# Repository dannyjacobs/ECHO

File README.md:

The External Calibrator for Hydrogen Arrays (ECHO) is a system for calibrating wide-field radio frequency arrays using a radio transmitter mounted on a drone.
Primarily targeting (but not exclusively limited to) arrays operating in the sub-GHz band targeting highly redshifted
21cm radiation from the early universe.

This repository contains software for planning missions and analyzing data. It also contains hardware designs for drones and mounts.

This is an open source project. Use and reuse is encouraged.  If you use this code or hardware designs please reference the github repo.
http://github.com/dannyjacobs/ECHO and cite [our 2017 paper](http://adsabs.harvard.edu/abs/2017PASP..129c5002J).  If you have improvements please fork and send a PR!

## Community
* We have an active "Slack Connect" channel, accessible to anyone with a Slack account.  To be invited, email [Danny Jacobs](dcjacob2@asu.edu)
* Project [Web page](http://danielcjacobs.com/ECHO)
* [Code Documentation](https://external-calibrator-for-hydrogen-arrays-echo.readthedocs.io)
* A [mailing list](https://groups.google.com/d/forum/astro_echo) exists

## Installation
Install prerequisites. We recommend the anaconda package manager
* healpy (note that as of Jan 2020 healpy is not available for Windows)
* matplotlib
* numpy
* scipy

Get this repo
`git clone https://github.com/dannyjacobs/ECHO.git`

Install using pip
```
cd ECHO
pip install .
```

## Organization
The code is organized into a few modules. The beam mapping pipeline steps are
1. Read and down-select drone telemetry
2. Read and down-select radio telescope data (varies per telescope, usually spectra vs time)
3. Match up drone positions and telescope measurements. (Sometimes referred to as zippering.)
4. Grid beam (including power map, sample counts and standard deviation)
5. Analyze results. Example analysis steps include:
  1. subtract transmitter model
  2. plot beam maps
  3. plot slices
  4. plot drone events and dynamics
  5. difference beams
### Modules

 #### `plot_utils.py`
 Functions for plotting, but also all functions relating to healpix gridding
 and manipulation including gridding.
  * `grid_to_healpix` :  grids aligned RF power vs XYZ position
 into a healpix map
  * `make_beam` :  downselects desired spectral channel, converts from latlon to XYZ and calls `grid_to_healpix`
  * `project_healpix` :  flattens from spherical healpix map to 2d gnomic projection
  * `rotate_hpm` :  rotates a healpix map about the polar axis. useful for plotting
  * Other functions, most of whom are deprecated.
 #### `read_utils.py`
 Functions for reading and writing drone and beam data. Drone log file formats
 are not well documented and change all the time.
  * `read_map` : replacement for healpy read function that respects nans
  * `write_map`: replacement for healpy write function that respect nans
  * `apm_version`: tries to determine the version of ardupilot that wrote a log file.
  * `read_apm_log_A_B_C` : reads an ardupilot log of version A_B_C
    * returns position_times, positions,
    * attitude_times, attitudes,
    * waypoint_times, waypoint_numbers
  * `read_echo_spectrum` : reads a spectrum data file output by the ECHO spectrum logger ca 2017 (signalhound + get_sh_spectra)
  * `read_orbcomm_spectrum` : reads a spectrum data file output by the Bradley orbcomm system (ca 2017)
  * `channel_select` : given a spectrum, list of frequencies, and desired frequency returns closest frequency and spectrum amplitude
  * `interp_rx`: interpolates received power onto the measured position time grid
  * `flag_angles` : flags outlier yaws input times,yaw_angles return matching flag array
  * `flag_waypoints` : flags a range of time around a list of waypoints
  * `apply_flagtimes` : Given a list of bad times, a buffer size and a time array, generate a flag table.
#### `position_utils.py`
 * `latlon2xy` : about what you think
 * `to_spherical` : xyz to spherical
#### `time_utils.py`
Most of these are of dubious necessity.
 * `unix_to_gps` : thin wrapper around astropy.Time
 * `gps_to_HMS` : convert GPS time to Hours Minutes Seconds, thin wrapper around
#### `server_utils.py`
Stuff developed to support real-time operations. This never worked very well with mavlink.
### Scripts
#### Jacobs 2017
Scripts used in the 2017 paper are all run in [one master shell script](https://github.com/dannyjacobs/ECHO_paper1/blob/master/scripts/make_plots.sh)
 * plot_yaw.py
 * plot_GB_pos_power_interp.py
 * ECHO_zipper.py
 * ECHO_mk_beam.py
 * plot_ECHO_GB_power_rms_counts.py
 * plot_ECHO_GB_maps.py
 * plot_GB_slices.py
 * ECHO_sub_tx_beam.py
 * plot_ECHO_GB_ratios.py
 * plot_GB_avg_slices.py
 * plot_MWAtile_slices.py
 * MWATilemodel2hpm.py
 * combine_MWAtile_maps.py

 #### Utility Scripts
  * valon_readwrite.py : program the valon transmitter
  * gen_spherical_flight_path.py : generate waypoints in a healpix pattern
  * CST_to_healpix.py : convert the beam file from CST Microwave studio to a healpix map. Note that this should eventually be replaced with [pyuvbeam](https://github.com/RadioAstronomySoftwareGroup/pyuvdata/blob/master/pyuvdata/uvbeam.py).

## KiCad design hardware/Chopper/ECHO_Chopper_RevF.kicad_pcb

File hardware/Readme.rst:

.. csv-table:: ECHO Version Summary
   :header: "Version", "Drone Make", "Drone Frame", "Drone Name", "Tx Mount", "Transmitter", "Antenna", "Flight Software"
   :widths: auto

   "1", "Mystery Inc.", "Octo", "Brain", " ", " ", "BicoLOG 5070", " "
   "2", "Flamewheel", "Quad", "Crater", " ", " ", "BicoLOG 5070", " "
   "3", "3D-Robotics", "X8", Pancake, " ", " ", BicoLOG 5070", " "
   "4", "3D-Robotics", "X8", Waffle, "`Sliding_Mount <https://github.com/dannyjacobs/ECHO/tree/master/hardware/STLs/04_Sliding_Mount>`_", "Blackbox", BicoLOG 5070", " "
   "5", "3D-Robotics", "X8", Killer, "`X8_Mount_v1 <https://github.com/dannyjacobs/ECHO/tree/master/hardware/STLs/05_X8_Mount_v1>`_", "Blackbox", BicoLOG 5070", " "
   "6", "Steadidrone Vader", "X8", "Vader", "`Vader_Mount <https://github.com/dannyjacobs/ECHO/tree/master/hardware/STLs/06_Vader_Mount>`_", "Blackbox", "BicoLOG 5070", "PX4"
   "7", "Yuneec", "Octo H520", "Yuneec", "`Yuneec_Mount <https://github.com/dannyjacobs/ECHO/tree/master/hardware/STLs/07_Yuneec_Mount>`_", "Valon 5009", "BicoLOG 5070", "Yuneec"
   "8", "3D-Robotics", "X8", "Killer", "`X8_Mount_v2 <https://github.com/dannyjacobs/ECHO/tree/master/hardware/STLs/08_X8_Mount_v2>`_", "Valon 5009", "BicoLOG 5070", "PX4"
   "9", "in house `bom <https://github.com/dannyjacobs/ECHO/blob/master/hardware/Chiropter%20BoM%20-%20Revised%20Build%20Sheet.pdf>`_, `build log <https://github.com/dannyjacobs/ECHO/blob/master/hardware/Chiropter%20Build%20Log.pdf>`_","Hex F550", "Chiropter", "`Chiropter Mount v1 (for Valon) <https://github.com/dannyjacobs/ECHO/tree/master/hardware/STLs/09_Chiropter_Mount_v1>`_, `Mount V2 for TituTx etc  <https://github.com/dannyjacobs/ECHO/tree/master/hardware/STLs/10_Chiropter_Mount_v2>`_","Valon 5009","BicoLOG 5070","PX4"

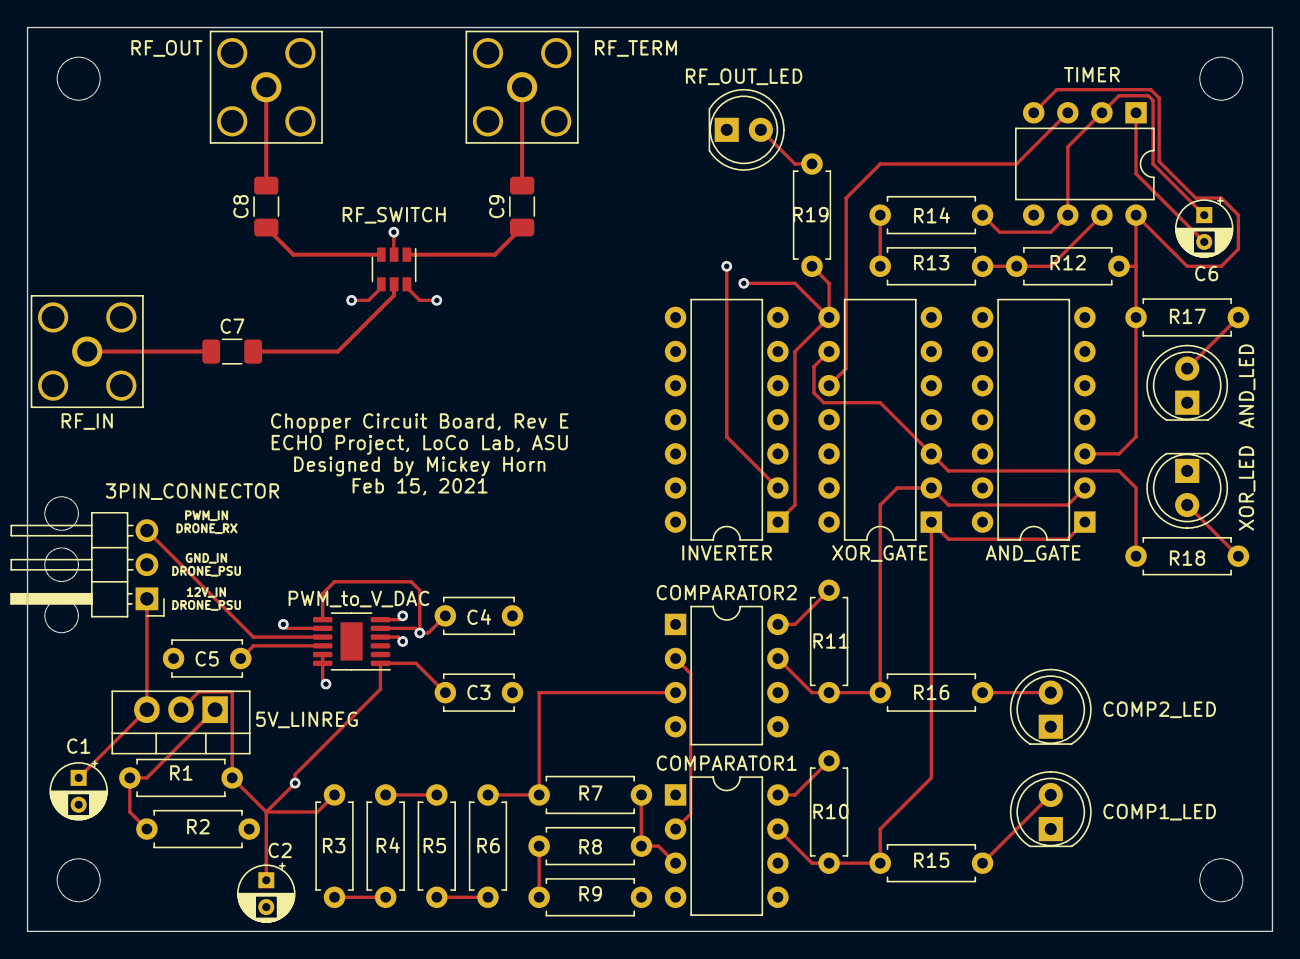
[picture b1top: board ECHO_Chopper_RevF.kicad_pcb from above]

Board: 4 copper layers, 92.7 x 67.3 mm, 46 parts (0 on the bottom side), 34 nets.

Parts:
3PIN_CONNECTOR: Conn_01x03_Male; PinHeader_1x03_P2.54mm_Horizontal
5V_LINREG: LM317_3PinPackage; TO-220-3_Vertical
AND_GATE: SN74LS08N; DIP-14_W7.62mm
AND_LED: LED; LED_D5.0mm
C1: 0.1uF; CP_Radial_D4.0mm_P2.00mm
C2, C6: 1uF; CP_Radial_D4.0mm_P2.00mm
C3, C4, C5: 0.15uF; C_Disc_D5.0mm_W2.5mm_P5.00mm
C7, C8, C9: 390pF; C_1206_3216Metric_Pad1.33x1.80mm_HandSolder
COMP1_LED, COMP2_LED: LED; LED_D5.0mm
COMPARATOR1, COMPARATOR2: LM311; DIP-8_W7.62mm
INVERTER: SN74LS04N; DIP-14_W7.62mm
PWM_to_V_DAC: LTC2644CMS-L12#PBF; MSOP-12-1EP_3x4mm_P0.65mm_EP1.65x2.85mm
R1, R15, R16, R17, R18, R19: 100; R_Axial_DIN0207_L6.3mm_D2.5mm_P7.62mm_Horizontal
R2: 300; R_Axial_DIN0207_L6.3mm_D2.5mm_P7.62mm_Horizontal
R3, R14: 100k; R_Axial_DIN0207_L6.3mm_D2.5mm_P7.62mm_Horizontal
R4: 47k; R_Axial_DIN0207_L6.3mm_D2.5mm_P7.62mm_Horizontal
R5: 22k; R_Axial_DIN0207_L6.3mm_D2.5mm_P7.62mm_Horizontal
R6: 5.6k; R_Axial_DIN0207_L6.3mm_D2.5mm_P7.62mm_Horizontal
R7: 2.2k; R_Axial_DIN0207_L6.3mm_D2.5mm_P7.62mm_Horizontal
R8, R9: 3.3k; R_Axial_DIN0207_L6.3mm_D2.5mm_P7.62mm_Horizontal
R10, R11: 20k; R_Axial_DIN0207_L6.3mm_D2.5mm_P7.62mm_Horizontal
R12: 15k; R_Axial_DIN0207_L6.3mm_D2.5mm_P7.62mm_Horizontal
R13: 200k; R_Axial_DIN0207_L6.3mm_D2.5mm_P7.62mm_Horizontal
RF_IN: Valon Input; SMA_Amphenol_132203-12_Horizontal
RF_OUT: BicoLOG Output; SMA_Amphenol_132203-12_Horizontal
RF_OUT_LED: LED; LED_D5.0mm
RF_SWITCH: HMC545AE; SOT-23-6
RF_TERM: Terminated Output; SMA_Amphenol_132203-12_Horizontal
TIMER: TLC555xP; DIP-8_W7.62mm
XOR_GATE: SN74LS86AN; DIP-14_W7.62mm
XOR_LED: LED; LED_D5.0mm

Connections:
/0.18V: COMPARATOR1.3, R7.2, R8.1
/0.24V: COMPARATOR2.3, R6.2, R7.1
/5V: 5V_LINREG.2, AND_GATE.14, C2.1, C3.1, C4.1, COMPARATOR1.8, COMPARATOR2.8, INVERTER.14, PWM_to_V_DAC.1, PWM_to_V_DAC.5, PWM_to_V_DAC.7, R1.1, R3.1, R10.2, R11.2, XOR_GATE.14
/12V: 3PIN_CONNECTOR.1, 5V_LINREG.3, C1.1
/PWM: 3PIN_CONNECTOR.3, PWM_to_V_DAC.9
GND: 3PIN_CONNECTOR.2, AND_GATE.7, AND_LED.1, C1.2, C2.2, C3.2, C4.2, C5.2, C6.2, COMP1_LED.1, COMP2_LED.1, COMPARATOR1.1, COMPARATOR1.4, COMPARATOR2.1, COMPARATOR2.4, INVERTER.7, PWM_to_V_DAC.4, PWM_to_V_DAC.6, PWM_to_V_DAC.8, PWM_to_V_DAC.11, PWM_to_V_DAC.12, R2.1, R9.2, RF_IN.2, RF_OUT.2, RF_OUT_LED.1, RF_SWITCH.2, RF_TERM.2, TIMER.1, XOR_GATE.7, XOR_LED.1
unnamed: 5V_LINREG.1, R1.2, R2.2
unnamed: AND_GATE.1, COMPARATOR1.7, R10.1, R15.1, XOR_GATE.1
unnamed: AND_GATE.2, COMPARATOR2.7, R11.1, R16.1, XOR_GATE.2
unnamed: AND_GATE.3, R12.2, R17.1, TIMER.4, TIMER.8
unnamed: AND_LED.2, R17.2
unnamed: C5.1, PWM_to_V_DAC.10
unnamed: C6.1, R14.2, TIMER.2, TIMER.6
unnamed: C7.1, RF_IN.1
unnamed: C7.2, RF_SWITCH.5
unnamed: C8.1, RF_SWITCH.3
unnamed: C8.2, RF_OUT.1
unnamed: C9.1, RF_SWITCH.1
unnamed: C9.2, RF_TERM.1
unnamed: COMP1_LED.2, R15.2
unnamed: COMP2_LED.2, R16.2
unnamed: COMPARATOR1.2, COMPARATOR2.2, PWM_to_V_DAC.2
unnamed: INVERTER.1, R19.2, RF_SWITCH.6, XOR_GATE.8
unnamed: INVERTER.2, RF_SWITCH.4
unnamed: R3.2, R4.1
unnamed: R4.2, R5.1
unnamed: R5.2, R6.1
unnamed: R8.2, R9.1
unnamed: R12.1, R13.2, TIMER.7
unnamed: R13.1, R14.1
unnamed: R18.1, XOR_LED.2
unnamed: R18.2, XOR_GATE.3, XOR_GATE.9
unnamed: R19.1, RF_OUT_LED.2
unnamed: TIMER.3, XOR_GATE.10

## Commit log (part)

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2015-12-29 Adding scripts
2016-01-04 Adding GPS scritps and test files
2016-03-16 Adding Docker instructions
2016-04-01 Docker functionality no longer needed
2016-05-03 Revised setup script
2016-05-03 Updated server and accumulation error handling
2016-05-04 Modified scripts to add a sequence of -1s when no valid GPS data available. Test data added to testing directory with scripts to modify existing data from previous experiments and create fake data.
2016-05-10 Updated plotting script
2016-05-10 Updated testing scripts
2016-05-16 Functionalizationizing
2016-05-24 Updated function files and associated scripts
2016-05-25 Updated for tmux support
2016-05-25 Fixed error message
2016-05-25 Modified library calls. ECHO_server_utils.py needs additional work
2016-05-26 Backtracking server code for global variable manipulations
2016-05-26 Updated plotting condition
2016-05-26 Updating plotting functions. ECHO_plot.py only works properly on Jacob's Macbook Pro. It does not work on the Linux machine or the new Mac.
2016-05-26 Plot drawing error potential fix
2016-05-26 Removed TkAgg backend use and replaced draw() with pause(0.001). Plotting problem seems to be solved.
2016-06-02 Reorganized ER data and made new compilation/grid scripts for ER data
2016-06-06 Updating ER data
2016-06-09 Updated post-processing portions of scripts. Tested on ER data for start/stop time and waypoint filtering.
2016-06-10 tweaking the README formatting
2016-06-10 README wording
2016-06-21 Updated GPS position scripts for tlog parsing from APM Planner
2016-06-22 Update read utils
2016-06-22 Accumulation queries ground station with time in GPS seconds
2016-06-22 Update file structure
2016-06-22 Updated plotting scripts for 1024 bin SH data
2016-06-22 Indentation problems fixed
2016-06-22 Needed 1024 bin resolution in ECHO_setup.sh for accum station
2016-07-06 Old pipeline and globbing integrated
2016-07-06 ER data/scripts in Google Drive
2016-07-15 Pushin ACTUAL ER code modifications
2016-07-15 Pushing modifications from ER 7/14/16
2016-07-22 Realtime spectrum script not working
2016-07-26 ECHO_plot_utils.py now uses the modified get_interp_val function. ECHO_plot.py can accept fits files for plotting.
2016-07-27 Moving modules to src.
2016-07-27 Renaming modules
2016-07-27 Adding gitignore
2016-08-18 Big refactor, moving lots of things into smaller function calls.
2016-08-18 Rebuilding a third pipeline that uses new functions.
    ECHO_zipper.py -> ECHO_mk_beam.py
2016-12-16 after lots of debugging replaced the rotate_hpm with one that actually works
2016-12-16 kill an annoying print statement
2017-06-26 CST to Healpix script
2018-06-29 Adding gnuradio-based spectrometer code. DOES NOT WORK YET
2018-06-30 added dc block from grc output
2018-06-30 scanning spectrometer works on x300!
2018-07-27 Moved gr-speclog out of scripts directory
2018-07-30 New folder with important figures, mplstyle
2018-07-30 Edited myglyph line to use correct path to image
2018-07-30 Move plots from paper1 in, remove non-scripts
2018-07-30 Added ECHO to package_data
2018-08-01 Edits to plot_slices.py to take in a test file as an input from the command line
2018-08-15 Adding x300 calibration notebook
2018-08-15 change frequency scanning to to have a start frequency
2018-08-15 refine the tuning and lengthen the integration time on the terminated load
2018-09-20 more calibration analysis
2018-10-21 Some tweaks during testing at ERAU
2018-10-25 adds set_gain
2018-10-30 changes to spectrum and log so danny can use in prescott I think
2018-10-30 adding spectrum est notebook
2018-11-02 more FM analysis of the weeklong data
2018-11-02 more FM analysis of the weeklong data2
2019-10-02 Update gen_spherical_flight_path
    Replacing v2 with v3 and removing that part in the name
2019-10-02 Current position removal
    Removed check that center position was within 100m of hard-coded coordinate
2019-10-02 annotations
    describing what each line does
2019-10-02 comments/notes
    walking myself through the code
2019-10-03 test usage
    adjusted the test usage comment as an example for how to run the code
2019-10-03 test usage
    matched actual usage for Chiropter Meyer full test
2019-10-03 adding velocity to waypoints
    user velocity input now goes into each waypoint
2019-10-03 1 more undo
    forgot to remove vel from print_MAV_WPT
2019-10-03 old code clean up, added defaults
    removed old code that is no longer being used in the script and added defaults to most options
2020-01-25 don't commit pycs
2020-01-25 README docs
2020-01-25 list of useful scripts
2020-01-25 Scripts
2020-01-30 Removed report and reduction folders, created temp folder for scripts to keep, updated readme with missing scripts from master script
2020-01-31 edit workflow to get proper branch
2020-02-03 fixed workflow dependency requirements
2020-02-03 Edited changelog to reflect recent changes
2020-02-03 fixing setup.py for this branch
2020-02-13 fixed a bunch of flake8 errors, added pycache to gitignore
2020-02-13 fixed .gitignore
2020-02-13 fixed .gitignore pycache again
2020-02-13 disabled pytest until initial tests are made
2020-02-13 Adding Chiropter parameter file
    From QGC, upload to other drones to copy settings
2020-02-13 fixed server_utils after checking old scripts, now passes flake8
2020-02-13 fixed typo
2020-02-13 Added comments for clarity
2020-02-20 first pass at updating for python 3
2020-02-20 removed spaces from runtests.yaml python list
2020-02-20 more runtest editing, get correct branch instead of cleanup
2020-02-25 ran state 1 futurize to convert to python 3
2020-02-25 disabled lines in server_utils causing exit, bugfix for testst, enabled testing on commit
2020-02-25 More edits to correct testing action
2020-02-25 fixed pytest command, removed coverage for now
2020-02-25 More tweaks to runtests
2020-02-25 more runtest tweaks
2020-02-25 added flask dependency
2020-03-05 Fixed optparse error, same error as test branch
2020-03-13 Added tlog_txt and ulog read utilities
2020-03-18 Added pyulog dependency for setup
2020-04-09 Added Observation class and associated methods, Sortie class and methods.
2020-04-10 More work on the interpolate, make refined data array including rx
2020-04-10 fixed some imports
2020-04-24 Fixes, options, and edits based on feedback
2020-04-24 added setup package for dependency
2020-04-24 fixed another dependency, fixed string formatter to be compatible with python 2
2020-05-16 Frequency channels now automatically read, interpolation changed from extrapolation, more plots, additional documentation
2020-06-11 Read in CST, mollview and gridded plots, some structure for future classes
2020-07-10 Added plotting functions: 3d Iso view, E and H slices. Added beam class, as well as dependency on UVBeam from pyuvdata.
2020-07-10 Added pyuvdata dependencies to setup args
2020-07-13 added autodocs extension
2020-07-21 More document creation, module reading now works mostly correctly, added basic pages for API and tutorials
2020-07-21 config files for readthedocs
2020-07-21 added pyulog requirement
2020-07-21 fixed image read
2020-07-21 added flask to requirements
2020-07-21 remove py27 from runtests
2020-07-23 documented how we're using uvbeam, added some overlooked plotting functions
2020-07-24 add build log and bom
2020-07-28 added summary table draft
2020-07-28 added echo summary table in txt format
2020-07-28 remove pdf and txt, new rst attempt
2020-07-28 align * lines
2020-07-28 3 spaces
2020-07-28 copy from another rst file to test
2020-07-28 copy from another st file to test
2020-07-28 add default csv-table
2020-07-28 tweak to our table
2020-07-28 clean up into 1 rst
2020-07-28 full table
2020-07-28 edited api doc page to reflect recent module changes
2020-07-29 added pre-commit config, file modifications after running pre-commit
2020-07-29 added config for circleci as a test, added some files modified by flake8 and missed previously
2020-07-29 more editing for circleci config, requirements now generated from requirements.txt
2020-07-29 tweak to circleci config
2020-07-30 cleaning up docs
2020-07-30 Changed version to 1.0.0 in prep for merger
2020-07-30 Update and rename ECHO_Summary.rst to ECHO_hardware_summary.rst
    Added links to STL files and build log
2020-07-30 Update README.md
    change rtd url
2020-08-13 added tuning2 freq_chan
2020-08-13 fixed error
2020-08-13 removed references to variables that are no longer used, add HP beam to power variable when created
2020-08-17 rx power dB conversion
2020-08-17 minor edits
2020-08-20 making editing suggestions to changelog
2020-08-20 fixing requirements and circleci config
2020-08-20 updated requirements to include flake8
2020-08-20 fixed whitespace issue with hardware summary
2020-08-20 CircleCI badge added to readme
2020-08-23 progress on tutorial, added images
2020-08-24 added link to paper and beam documentation
2020-08-24 fixed setup image error
2020-08-25 added installation page
2020-08-27 fixes by running pre-commit
2020-09-03 added workflow chart and modified tutorial accordingly
2020-09-05 modified workflow and tutorial
2020-09-10 Added tests for beams, obs, time utilities. Fixed polar plot error.
2020-09-15 reverted spell check in difference_beam() function
2020-09-24 reverted function changes
2020-09-24 Added some read tests using test data
2020-10-15 fixed whitespace issue in precommit
2020-10-15 Added shortened hdf5 file, test modified appropriately
2020-10-29 minor spacing edits
2020-10-29 Added pytest-cov to requirements
2020-10-29 fix pytest command to include all files, not just tests
2020-10-29 More pytest tweaks
2020-10-29 Added coverage options to setup.cfg, referenced this in pytest
2020-10-29 testing fix found online, involving __init__.py
2020-10-29 Specify source in setup.cfg, tweak pytest command
2020-10-29 Added coverage to requirements.txt, tweaked pytest to show coverage in terminal as well as generate report
2020-11-05 More circleci tweaks, edited version in setup.py
2020-11-05 Update README.md
    CodeCov badge added, will begin working once pushed to master.
2020-12-03 fixed observations.py sorting bug
2021-02-03 putting analysis in its own directory
2021-02-04 undeleting file
2021-03-22 Updated URL for git clone command
2021-04-17 Update readme
    advertise slack channel.
    make links be links.
2021-04-17 experimental github page
2021-04-17 add title
2021-04-17 add memos
2021-04-17 add memo notes
2021-04-17 add presentations
2021-04-18 add logos
2021-04-18 try wide
2021-04-18 space
2021-04-18 Add notes
2021-04-24 fixed error caused by comment
2021-04-25 change to minimal-mistakes
2021-04-26 add gemfile
2021-04-26 update to gh-pages 214
2021-04-28 add/organize images
2021-04-28 cleanup images
2021-04-28 add font size override
    the default font of 16 is just too large
2021-04-28 template post
2021-04-28 default layout breaks things
2021-04-28 gemfile works
    it does
2021-04-28 _config works
2021-05-08 add font awesome
2021-05-08 update header and sidebar links
    add fa icons, comment a few pages that don't exist yet
2021-05-08 add faqs
2021-05-08 Update about
2021-05-08 add images
2021-05-08 create 404 page
2021-05-08 expand home page
2021-05-08 link to github discussions
2021-05-08 words
2021-05-08 debugging deploy
    switch to github-pages gem for remote compile
2021-05-08 undo
2021-05-08 fix workflow bug
2021-05-08 gemfile for good build
2021-05-08 update gem lock again
    working error on workflow
2021-05-08 use a runner that exists
2021-05-08 deploy: ef00ddc3cec6e4f688f2c56c3160948386be612e
2021-05-08 deploy: b0b1b453b7bd8fcc8ed318249509c897ae7ca067
2021-05-08 fix filenames
2021-05-08 change header image
2021-05-08 add readme
2021-05-09 add photo album link
2021-05-09 images
2021-05-09 hardware edits
2021-05-09 deploy: 403b66e866584b8be995508e95ceb4b1a31cd401
2022-08-29 break the drone table
2022-08-29 add chopper
2022-09-06 add chopper memos
2022-09-06 fix whitespace
2022-09-06 deploy: ad4b6db471a7a5144e7de329417ed21ae9290d4b
2023-02-10 fix formatting
    rst is so fragile
2023-05-19 Fixed a typo in gen_spherical_flight_path.py
